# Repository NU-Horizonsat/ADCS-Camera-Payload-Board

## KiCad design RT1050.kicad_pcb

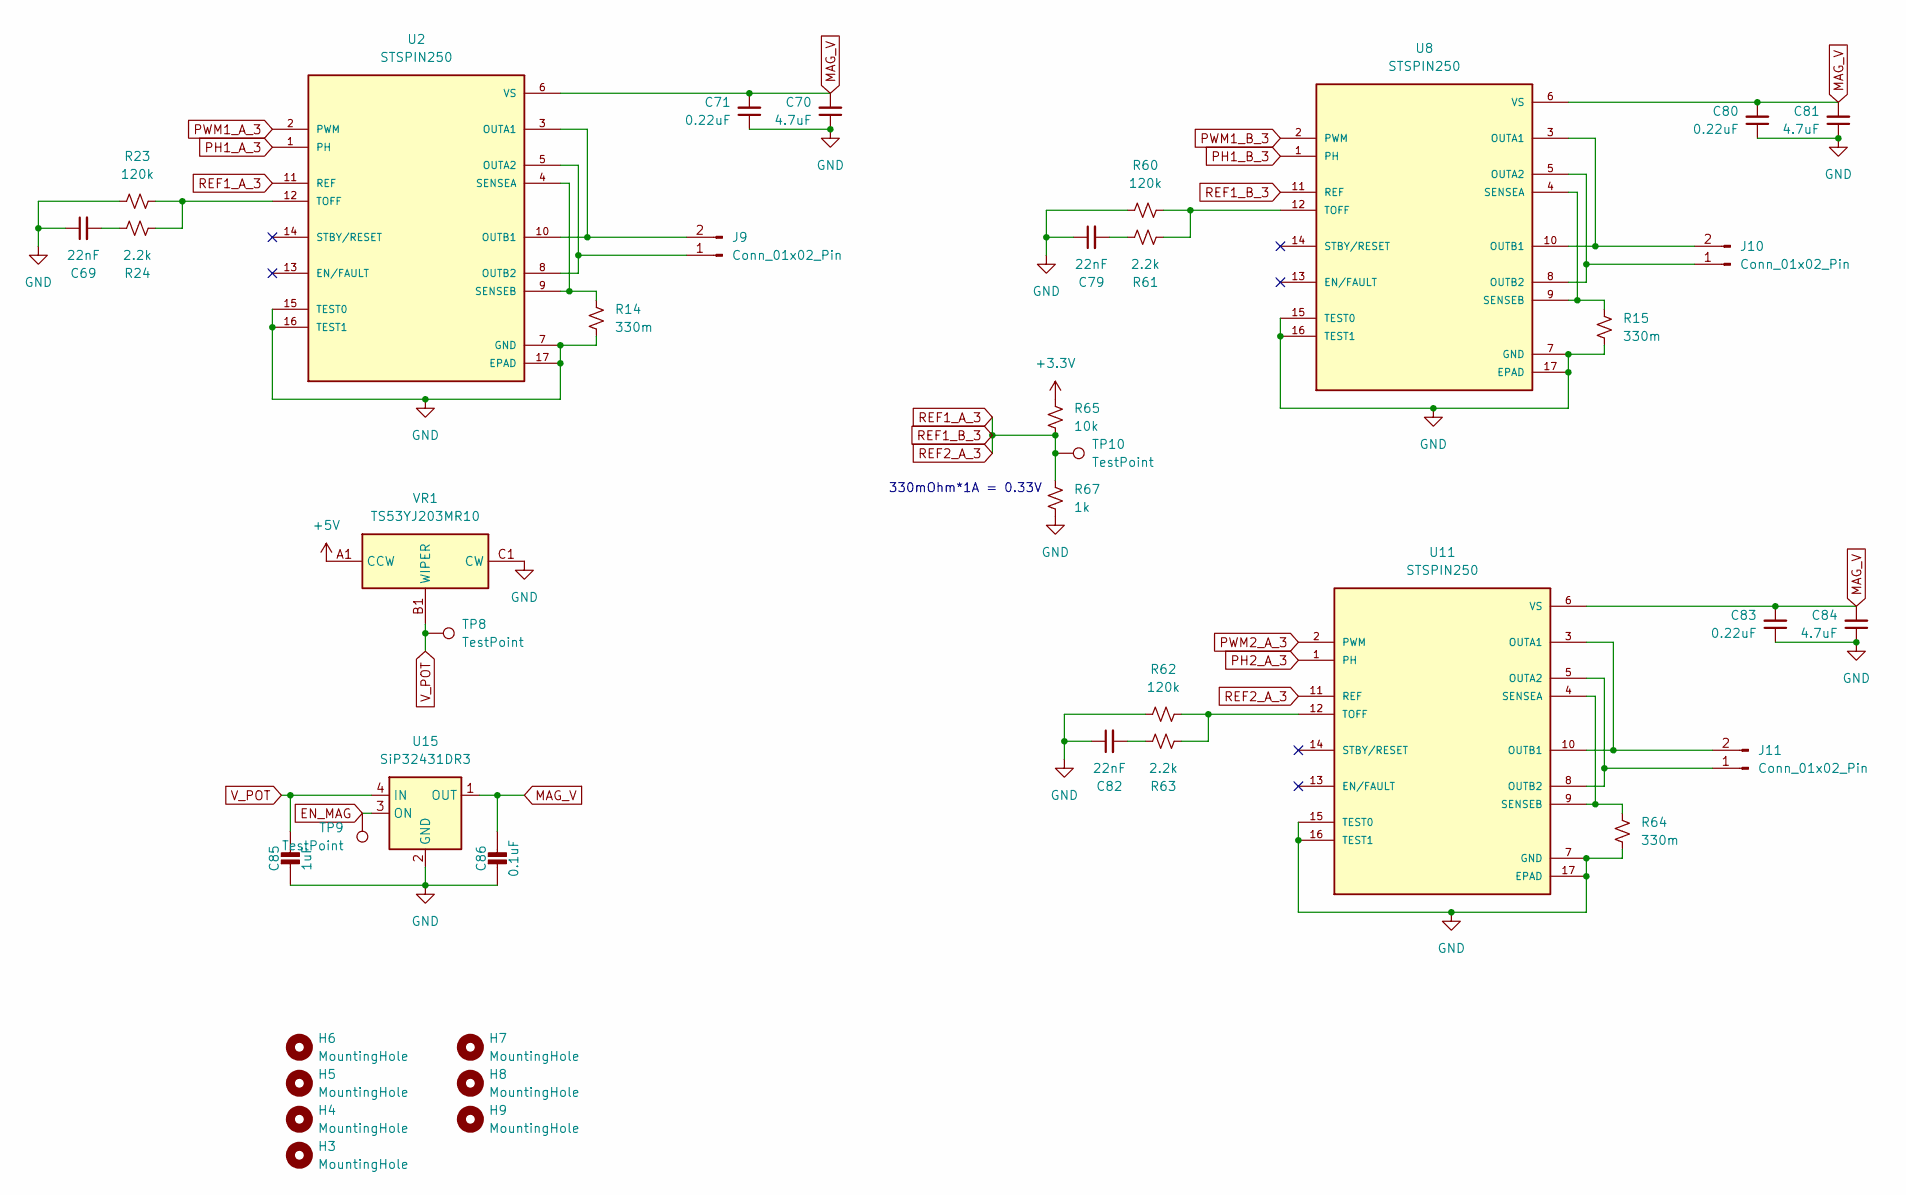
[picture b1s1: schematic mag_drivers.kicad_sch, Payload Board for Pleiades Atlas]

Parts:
C69, C79, C82: 22nF; C_0201_0603Metric
C70, C81, C84: 4.7uF; C_0201_0603Metric
C71, C80, C83: 0.22uF; C_0201_0603Metric
C85: 1uF; C_0402_1005Metric
C86: 0.1uF; C_0402_1005Metric
H3, H4, H5, H6, H7, H8, H9: MountingHole; MountingHole_2.5mm_Pad
J9, J10, J11: Conn_01x02_Pin; JST_SH_BM02B-SRSS-TB_1x02-1MP_P1.00mm_Vertical
R14, R15, R64: 330m; R_0402_1005Metric
R23, R60, R62: 120k; R_0402_1005Metric
R24, R61, R63: 2.2k; R_0402_1005Metric
R65: 10k; R_0402_1005Metric
R67: 1k; R_0402_1005Metric
TP8, TP9, TP10: TestPoint; TestPoint_Pad_D1.5mm
U2, U8, U11: STSPIN250; QFN50P300X300X100-17N; PARTREV 2
U15: SiP32431DR3; SOT-363_SC-70-6
VR1: TS53YJ203MR10; Mouser Part Number 72-TS53YJ-20K

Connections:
EN_MAG: TP9.1, U15.3 (ON); also elsewhere on the board
GND: C69.1, C70.1, C71.1, C79.1, C80.1, C81.1, C82.1, C83.1, C84.1, C85.2, C86.2, R14.2, R15.2, R23.1, R60.1, R62.1, R64.2, R67.1, U2.7 (GND), U2.15 (TEST0), U2.16 (TEST1), U2.17 (EPAD), U8.7 (GND), U8.15 (TEST0), U8.16 (TEST1), U8.17 (EPAD), U11.7 (GND), U11.15 (TEST0), U11.16 (TEST1), U11.17 (EPAD), U15.2 (GND), U15.5 (GND), VR1.C1 (CW); also elsewhere on the board
MAG_V: C70.2, C71.2, C80.2, C81.2, C83.2, C84.2, C86.1, U2.6 (VS), U8.6 (VS), U11.6 (VS), U15.1 (OUT)
unnamed: C69.2, R24.2
unnamed: C79.2, R61.2
unnamed: C82.2, R63.2
unnamed: J9.1, U2.5 (OUTA2), U2.8 (OUTB2)
unnamed: J9.2, U2.3 (OUTA1), U2.10 (OUTB1)
unnamed: J10.1, U8.5 (OUTA2), U8.8 (OUTB2)
unnamed: J10.2, U8.3 (OUTA1), U8.10 (OUTB1)
unnamed: J11.1, U11.5 (OUTA2), U11.8 (OUTB2)
unnamed: J11.2, U11.3 (OUTA1), U11.10 (OUTB1)
unnamed: R14.1, U2.4 (SENSEA), U2.9 (SENSEB)
unnamed: R23.2, R24.1, U2.12 (TOFF)
unnamed: R15.1, U8.4 (SENSEA), U8.9 (SENSEB)
unnamed: R60.2, R61.1, U8.12 (TOFF)
unnamed: R64.1, U11.4 (SENSEA), U11.9 (SENSEB)
unnamed: R62.2, R63.1, U11.12 (TOFF)
PH1_A_3: U2.1 (PH); also elsewhere on the board
PH1_B_3: U8.1 (PH); also elsewhere on the board
PH2_A_3: U11.1 (PH); also elsewhere on the board
PWM1_A_3: U2.2 (PWM); also elsewhere on the board
PWM1_B_3: U8.2 (PWM); also elsewhere on the board
PWM2_A_3: U11.2 (PWM); also elsewhere on the board
REF1_A_3: R65.1, R67.2, TP10.1, U2.11 (REF), U8.11 (REF), U11.11 (REF)
VBUS: VR1.A1 (CCW); also elsewhere on the board
V_POT: C85.1, TP8.1, U15.4 (IN), VR1.B1 (WIPER)

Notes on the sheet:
330mOhm*1A = 0.33V

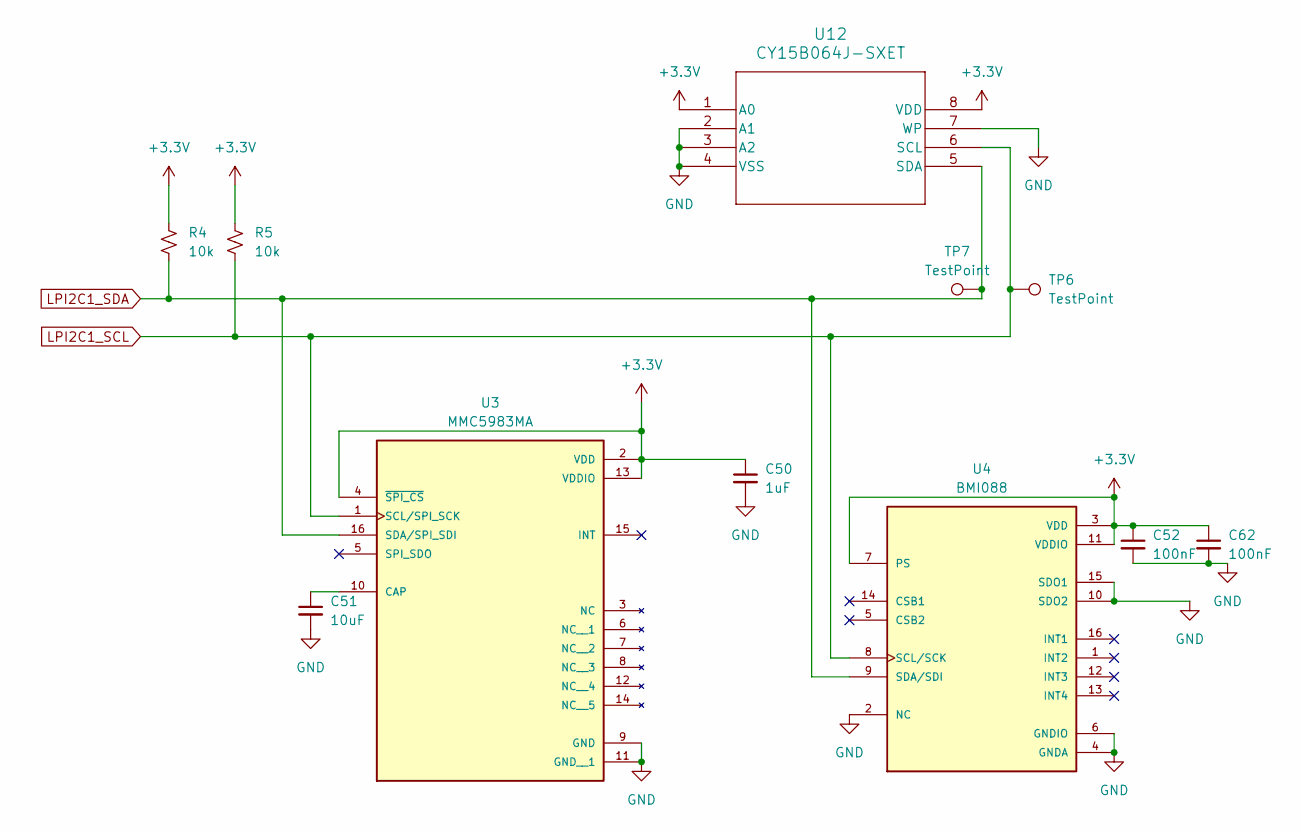
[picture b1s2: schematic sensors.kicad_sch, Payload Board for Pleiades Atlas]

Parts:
C50: 1uF; C_0201_0603Metric
C51: 10uF; C_0402_1005Metric
C52, C62: 100nF; C_0201_0603Metric
R4, R5: 10k; R_0402_1005Metric
TP6, TP7: TestPoint; TestPoint_Pad_D1.5mm
U3: MMC5983MA; MMC5983MA_MEM; PARTREV A
U4: BMI088; QFN_BMI085_BOS
U12: CY15B064J-SXET; SO8_CY15_CYP

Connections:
GND: C50.2, C51.2, C52.2, C62.2, U3.9 (GND), U3.11 (GND__1), U4.2 (NC), U4.4 (GNDA), U4.6 (GNDIO), U4.10 (SDO2), U4.15 (SDO1), U12.2 (A1), U12.3 (A2), U12.4 (VSS), U12.7 (WP); also elsewhere on the board
LPI2C1_SCL: R5.2, TP6.1, U3.1 (SCL/SPI_SCK), U4.8 (SCL/SCK), U12.6 (SCL); also elsewhere on the board
LPI2C1_SDA: R4.2, TP7.1, U3.16 (SDA/SPI_SDI), U4.9 (SDA/SDI), U12.5 (SDA); also elsewhere on the board
unnamed: C51.1, U3.10 (CAP)

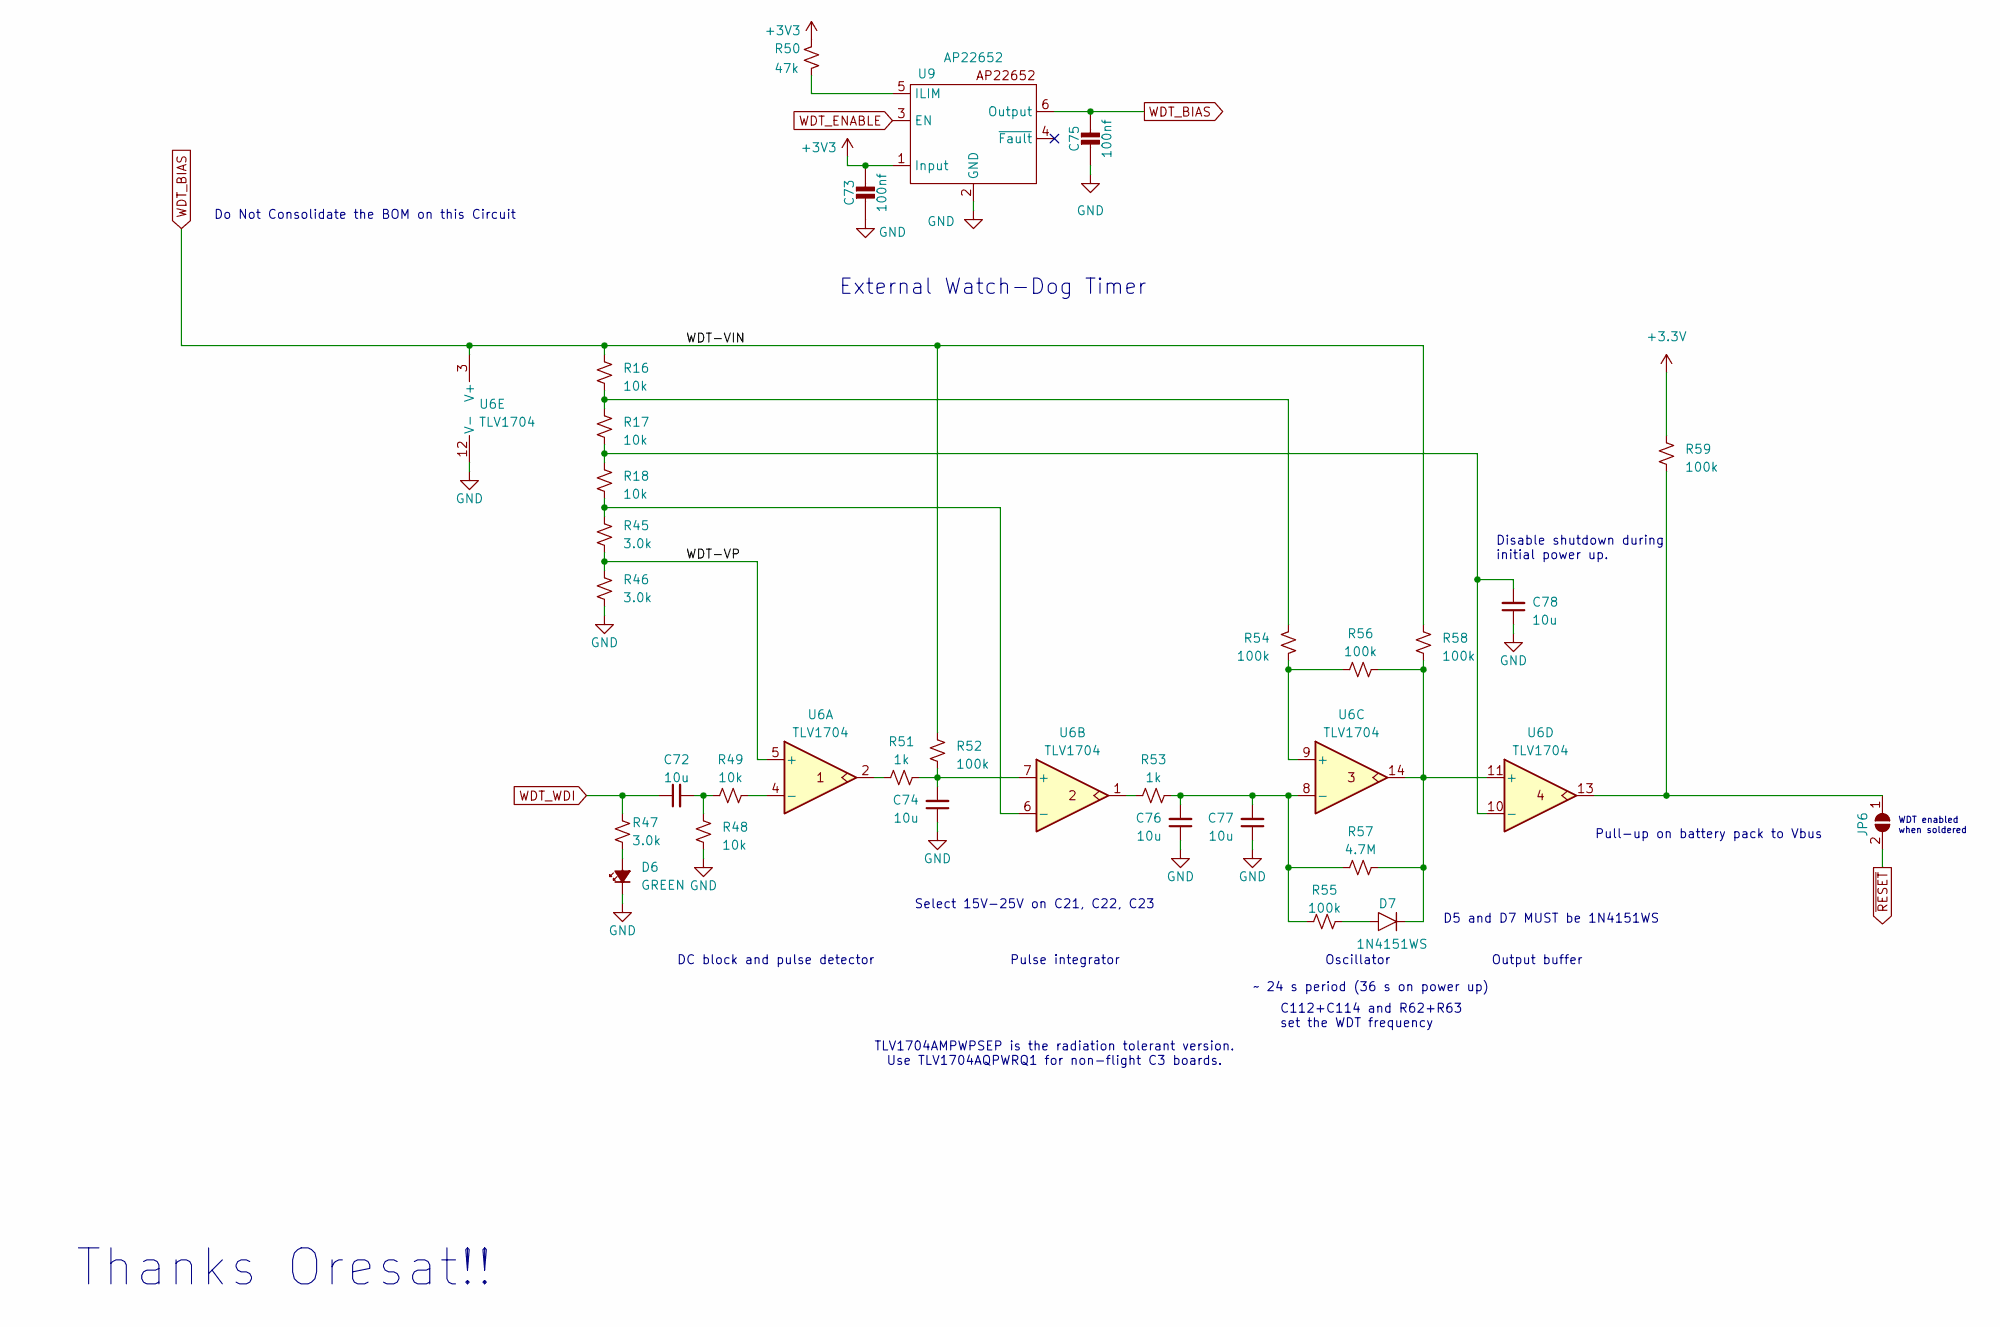
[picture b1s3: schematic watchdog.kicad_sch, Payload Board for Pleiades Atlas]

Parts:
C72, C74, C76, C77, C78: 10u; C_0603_1608Metric; MPN GRT188R61C106KE13D
C73, C75: 100nf; C_0402_1005Metric
D6: GREEN; LED_0603_1608Metric; MPN 150060GS75000
D7: 1N4151WS; D_SOD-323; MPN 1N4151WS-E3-08
JP6: SolderJumper_2_Open; SolderJumper-2_P1.3mm_Open_RoundedPad1.0x1.5mm
R16, R17, R18, R48, R49: 10k; R_0402_1005Metric; MPN RMCF0603FT10K0
R45, R46, R47: 3.0k; R_0402_1005Metric; MPN RMCF0603FT3K00
R50: 47k; R_0402_1005Metric; MPN RMCF0603FT47K0
R51, R53: 1k; R_0402_1005Metric; MPN RMCF0603FT1K00
R52, R54, R55, R56, R58, R59: 100k; R_0402_1005Metric; MPN RMCF0603FT100K
R57: 4.7M; R_0402_1005Metric; MPN RMCF0603FT4M70
U6: TLV1704; TSSOP-14_4.4x5mm_P0.65mm; MPN TLV1704AQPWRQ1
U9: AP22652; SOT95P280X145-6N

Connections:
/Watchdog/WDT-VP: R45.2, R46.1, U6.5 (+)
GND: C73.2, C74.1, C75.2, C76.1, C77.1, C78.1, D6.1 (K), R46.2, R48.2, U6.12 (V-), U9.2 (GND); also elsewhere on the board
unnamed: C72.2, R48.1, R49.1
unnamed: D6.2 (A), R47.2
unnamed: D7.2, R55.1
unnamed: JP6.1 (A), R59.1, U6.13
unnamed: R16.2, R17.1, R54.2
unnamed: R51.1, U6.2
unnamed: R53.1, U6.1
unnamed: R49.2, U6.4 (-)
unnamed: C74.2, R51.2, R52.2, U6.7 (+)
unnamed: R18.2, R45.1, U6.6 (-)
unnamed: R54.1, R56.1, U6.9 (+)
unnamed: C76.2, C77.2, R53.2, R55.2, R57.2, U6.8 (-)
unnamed: D7.1, R56.2, R57.1, R58.1, U6.11 (+), U6.14
unnamed: C78.2, R17.2, R18.1, U6.10 (-)
unnamed: R50.2, U9.5 (ILIM)
WDT_BIAS: C75.1, R16.1, R52.1, R58.2, U6.3 (V+), U9.6 (Output)
WDT_ENABLE: U9.3 (EN); also elsewhere on the board
WDT_WDI: C72.1, R47.1; also elsewhere on the board
~RESET: JP6.2 (B); also elsewhere on the board

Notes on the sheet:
Disable shutdown during initial power up.
WDT enabled when soldered
DC block and pulse detector
Thanks Oresat!!
Select 15V-25V on C21, C22, C23
Pulse integrator
~ 24 s period (36 s on power up)
C112+C114 and R62+R63 set the WDT frequency
Oscillator
TLV1704AMPWPSEP is the radiation tolerant version. Use TLV1704AQPWRQ1 for non-flight C3 boards.
Output buffer
Do Not Consolidate the BOM on this Circuit
Pull-up on battery pack to Vbus
External Watch-Dog Timer
D5 and D7 MUST be 1N4151WS

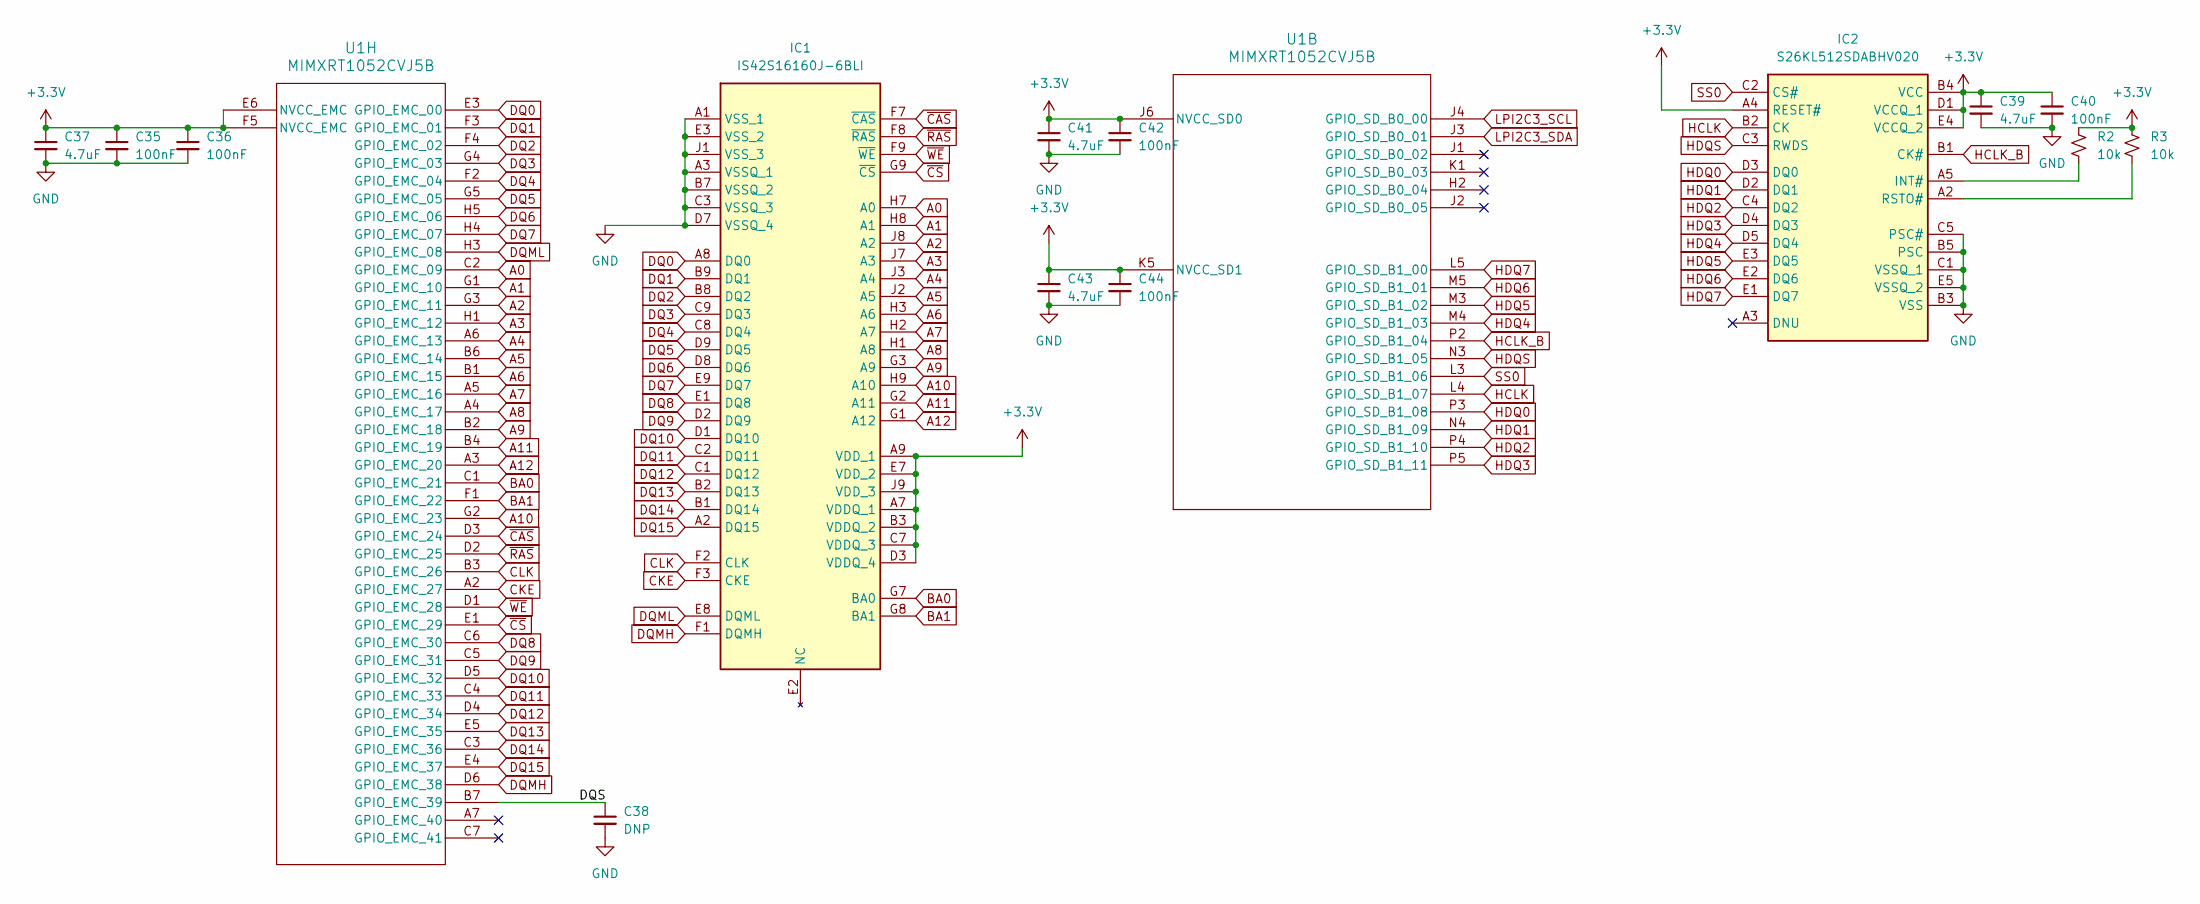
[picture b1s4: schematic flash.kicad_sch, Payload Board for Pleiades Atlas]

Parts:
C35, C36, C40, C42, C44: 100nF; C_0201_0603Metric
C37, C39, C41, C43: 4.7uF; C_0201_0603Metric
C38: DNP; C_0201_0603Metric
IC1: IS42S16160J-6BLI; BGA54C80P9X9_800X800X120; Mouser Part Number 870-42S16160J6BLI
IC2: S26KL512SDABHV020; BGA24C100P5X5_600X800X100; Mouser Part Number 727-26KS512SDPBHV020
R2, R3: 10k; R_0402_1005Metric
U1: MIMXRT1052CVJ5B; MAPBGA196_12X12

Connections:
/Flash & Memory/DQS: C38.1, U1.B7 (GPIO_EMC_39)
A0: IC1.H7 (A0), U1.C2 (GPIO_EMC_09)
A1: IC1.H8 (A1), U1.G1 (GPIO_EMC_10)
A2: IC1.J8 (A2), U1.G3 (GPIO_EMC_11)
A3: IC1.J7 (A3), U1.H1 (GPIO_EMC_12)
A4: IC1.J3 (A4), U1.A6 (GPIO_EMC_13)
A5: IC1.J2 (A5), U1.B6 (GPIO_EMC_14)
A6: IC1.H3 (A6), U1.B1 (GPIO_EMC_15)
A7: IC1.H2 (A7), U1.A5 (GPIO_EMC_16)
A8: IC1.H1 (A8), U1.A4 (GPIO_EMC_17)
A9: IC1.G3 (A9), U1.B2 (GPIO_EMC_18)
A10: IC1.H9 (A10), U1.G2 (GPIO_EMC_23)
A11: IC1.G2 (A11), U1.B4 (GPIO_EMC_19)
A12: IC1.G1 (A12), U1.A3 (GPIO_EMC_20)
BA0: IC1.G7 (BA0), U1.C1 (GPIO_EMC_21)
BA1: IC1.G8 (BA1), U1.F1 (GPIO_EMC_22)
CKE: IC1.F3 (CKE), U1.A2 (GPIO_EMC_27)
CLK: IC1.F2 (CLK), U1.B3 (GPIO_EMC_26)
DQ0: IC1.A8 (DQ0), U1.E3 (GPIO_EMC_00)
DQ1: IC1.B9 (DQ1), U1.F3 (GPIO_EMC_01)
DQ2: IC1.B8 (DQ2), U1.F4 (GPIO_EMC_02)
DQ3: IC1.C9 (DQ3), U1.G4 (GPIO_EMC_03)
DQ4: IC1.C8 (DQ4), U1.F2 (GPIO_EMC_04)
DQ5: IC1.D9 (DQ5), U1.G5 (GPIO_EMC_05)
DQ6: IC1.D8 (DQ6), U1.H5 (GPIO_EMC_06)
DQ7: IC1.E9 (DQ7), U1.H4 (GPIO_EMC_07)
DQ8: IC1.E1 (DQ8), U1.C6 (GPIO_EMC_30)
DQ9: IC1.D2 (DQ9), U1.C5 (GPIO_EMC_31)
DQ10: IC1.D1 (DQ10), U1.D5 (GPIO_EMC_32)
DQ11: IC1.C2 (DQ11), U1.C4 (GPIO_EMC_33)
DQ12: IC1.C1 (DQ12), U1.D4 (GPIO_EMC_34)
DQ13: IC1.B2 (DQ13), U1.E5 (GPIO_EMC_35)
DQ14: IC1.B1 (DQ14), U1.C3 (GPIO_EMC_36)
DQ15: IC1.A2 (DQ15), U1.E4 (GPIO_EMC_37)
DQMH: IC1.F1 (DQMH), U1.D6 (GPIO_EMC_38)
DQML: IC1.E8 (DQML), U1.H3 (GPIO_EMC_08)
GND: C35.2, C36.2, C37.2, C38.2, C39.2, C40.2, C41.2, C42.2, C43.2, C44.2, IC1.A1 (VSS_1), IC1.A3 (VSSQ_1), IC1.B7 (VSSQ_2), IC1.C3 (VSSQ_3), IC1.D7 (VSSQ_4), IC1.E3 (VSS_2), IC1.J1 (VSS_3), IC2.B3 (VSS), IC2.B5 (PSC), IC2.C1 (VSSQ_1), IC2.C5 (PSC#), IC2.E5 (VSSQ_2); also elsewhere on the board
HCLK: IC2.B2 (CK), U1.L4 (GPIO_SD_B1_07)
HCLK_B: IC2.B1 (CK#), U1.P2 (GPIO_SD_B1_04)
HDQ0: IC2.D3 (DQ0), U1.P3 (GPIO_SD_B1_08)
HDQ1: IC2.D2 (DQ1), U1.N4 (GPIO_SD_B1_09)
HDQ2: IC2.C4 (DQ2), U1.P4 (GPIO_SD_B1_10)
HDQ3: IC2.D4 (DQ3), U1.P5 (GPIO_SD_B1_11)
HDQ4: IC2.D5 (DQ4), U1.M4 (GPIO_SD_B1_03)
HDQ5: IC2.E3 (DQ5), U1.M3 (GPIO_SD_B1_02)
HDQ6: IC2.E2 (DQ6), U1.M5 (GPIO_SD_B1_01)
HDQ7: IC2.E1 (DQ7), U1.L5 (GPIO_SD_B1_00)
HDQS: IC2.C3 (RWDS), U1.N3 (GPIO_SD_B1_05)
LPI2C3_SCL: U1.J4 (GPIO_SD_B0_00); also elsewhere on the board
LPI2C3_SDA: U1.J3 (GPIO_SD_B0_01); also elsewhere on the board
unnamed: IC2.A5 (INT#), R2.2
unnamed: IC2.A2 (RSTO#), R3.2
SS0: IC2.C2 (CS#), U1.L3 (GPIO_SD_B1_06)
~CAS: IC1.F7 (~CAS), U1.D3 (GPIO_EMC_24)
~CS: IC1.G9 (~CS), U1.E1 (GPIO_EMC_29)
~RAS: IC1.F8 (~RAS), U1.D2 (GPIO_EMC_25)
~WE: IC1.F9 (~WE), U1.D1 (GPIO_EMC_28)

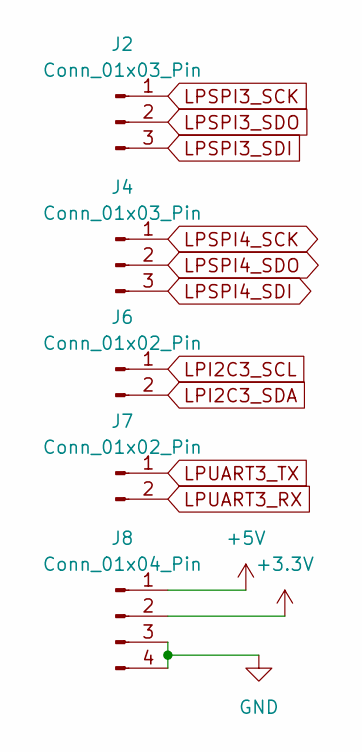
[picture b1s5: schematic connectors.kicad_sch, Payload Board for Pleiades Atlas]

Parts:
J2, J4: Conn_01x03_Pin; PinHeader_1x03_P2.54mm_Vertical
J6, J7: Conn_01x02_Pin; PinHeader_1x02_P2.54mm_Vertical
J8: Conn_01x04_Pin; PinHeader_1x04_P2.54mm_Vertical

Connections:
GND: J8.3, J8.4; also elsewhere on the board
GPIO_B0_08: J7.1; also elsewhere on the board
GPIO_B0_09: J7.2; also elsewhere on the board
LPI2C3_SCL: J6.1; also elsewhere on the board
LPI2C3_SDA: J6.2; also elsewhere on the board
LPSPI3_SCK: J2.1; also elsewhere on the board
LPSPI3_SDI: J2.3; also elsewhere on the board
LPSPI3_SDO: J2.2; also elsewhere on the board
LPSPI4_SCK: J4.1; also elsewhere on the board
LPSPI4_SDI: J4.3; also elsewhere on the board
LPSPI4_SDO: J4.2; also elsewhere on the board
VBUS: J8.1; also elsewhere on the board

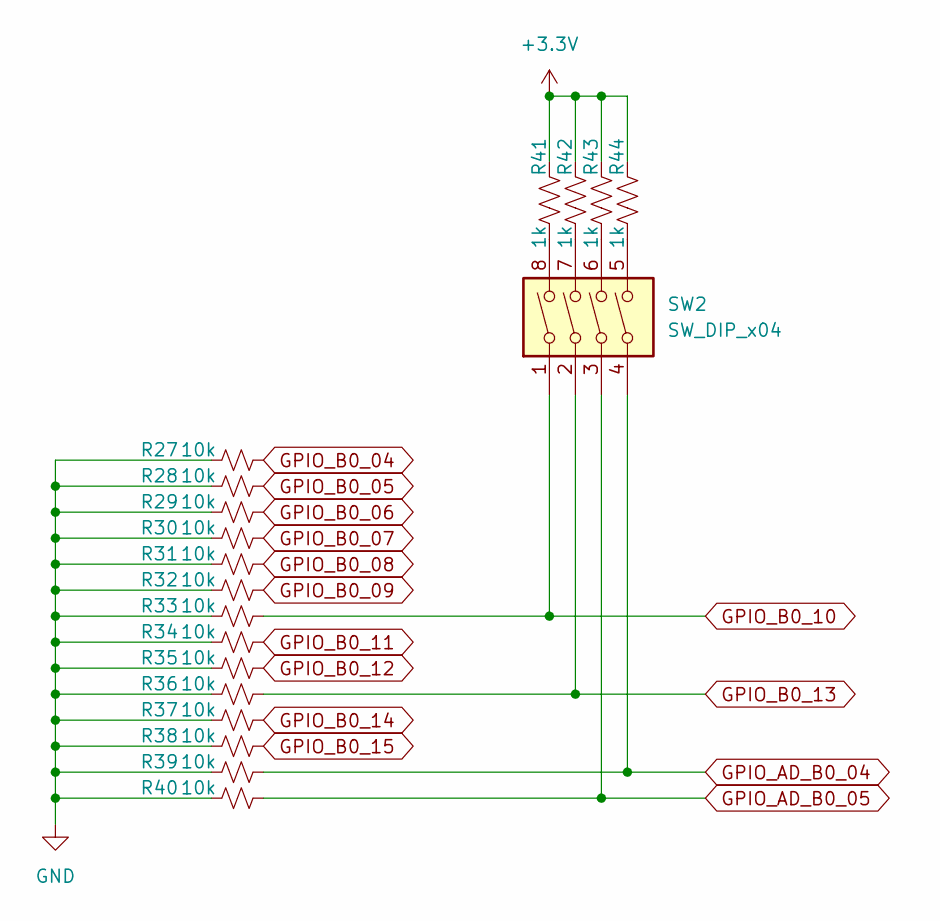
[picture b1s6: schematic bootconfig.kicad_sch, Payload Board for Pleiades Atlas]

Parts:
R27, R28, R29, R30, R31, R32, R33, R34, R35, R36, R37, R38, R39, R40: 10k; R_0402_1005Metric
R41, R42, R43, R44: 1k; R_0402_1005Metric
SW2: SW_DIP_x04; SW_DIP_SPSTx04_Slide_Copal_CHS-04A_W5.08mm_P1.27mm_JPin

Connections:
GND: R27.1, R28.1, R29.1, R30.1, R31.1, R32.1, R33.1, R34.1, R35.1, R36.1, R37.1, R38.1, R39.1, R40.1; also elsewhere on the board
GPIO_AD_B0_04: R39.2, SW2.4; also elsewhere on the board
GPIO_AD_B0_05: R40.2, SW2.3; also elsewhere on the board
GPIO_B0_04: R27.2; also elsewhere on the board
GPIO_B0_05: R28.2; also elsewhere on the board
GPIO_B0_06: R29.2; also elsewhere on the board
GPIO_B0_07: R30.2; also elsewhere on the board
GPIO_B0_08: R31.2; also elsewhere on the board
GPIO_B0_09: R32.2; also elsewhere on the board
GPIO_B0_10: R33.2, SW2.1; also elsewhere on the board
GPIO_B0_11: R34.2; also elsewhere on the board
GPIO_B0_12: R35.2; also elsewhere on the board
GPIO_B0_13: R36.2, SW2.2; also elsewhere on the board
GPIO_B0_14: R37.2; also elsewhere on the board
GPIO_B0_15: R38.2; also elsewhere on the board
unnamed: R41.2, SW2.8
unnamed: R42.2, SW2.7
unnamed: R43.2, SW2.6
unnamed: R44.2, SW2.5

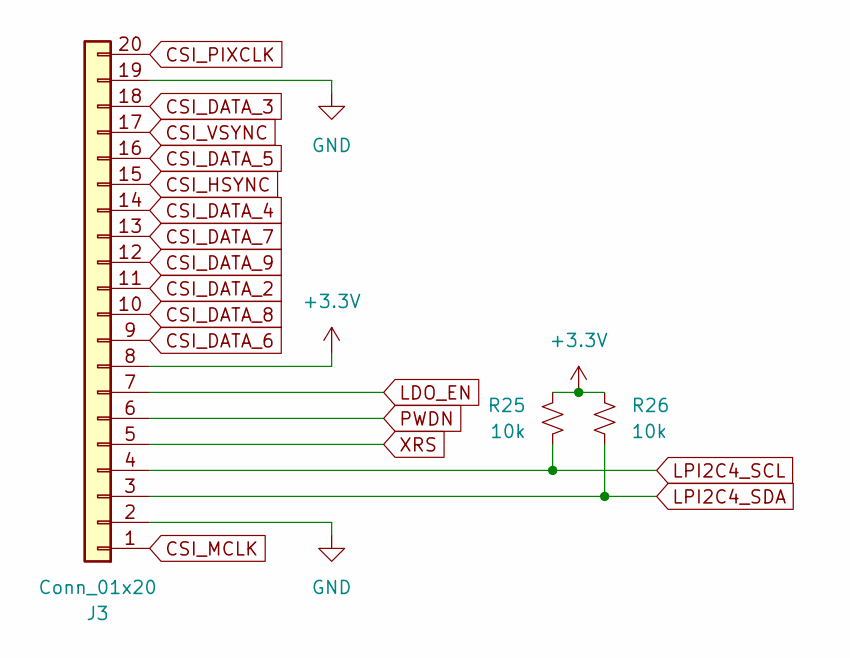
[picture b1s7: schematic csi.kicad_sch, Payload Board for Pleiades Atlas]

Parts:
J3: Conn_01x20; TE_2-1734839-0_1x20-1MP_P0.5mm_Horizontal
R25, R26: 10k; R_0402_1005Metric

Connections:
CSI_DATA_2: J3.11; also elsewhere on the board
CSI_DATA_3: J3.18; also elsewhere on the board
CSI_DATA_4: J3.14; also elsewhere on the board
CSI_DATA_5: J3.16; also elsewhere on the board
CSI_DATA_6: J3.9; also elsewhere on the board
CSI_DATA_7: J3.13; also elsewhere on the board
CSI_DATA_8: J3.10; also elsewhere on the board
CSI_DATA_9: J3.12; also elsewhere on the board
CSI_HSYNC: J3.15; also elsewhere on the board
CSI_MCLK: J3.1; also elsewhere on the board
CSI_PIXCLK: J3.20; also elsewhere on the board
CSI_VSYNC: J3.17; also elsewhere on the board
GND: J3.2, J3.19; also elsewhere on the board
LDO_EN: J3.7; also elsewhere on the board
LPI2C4_SCL: J3.4, R25.2; also elsewhere on the board
LPI2C4_SDA: J3.3, R26.2; also elsewhere on the board
PWDN: J3.6; also elsewhere on the board
XRS: J3.5; also elsewhere on the board

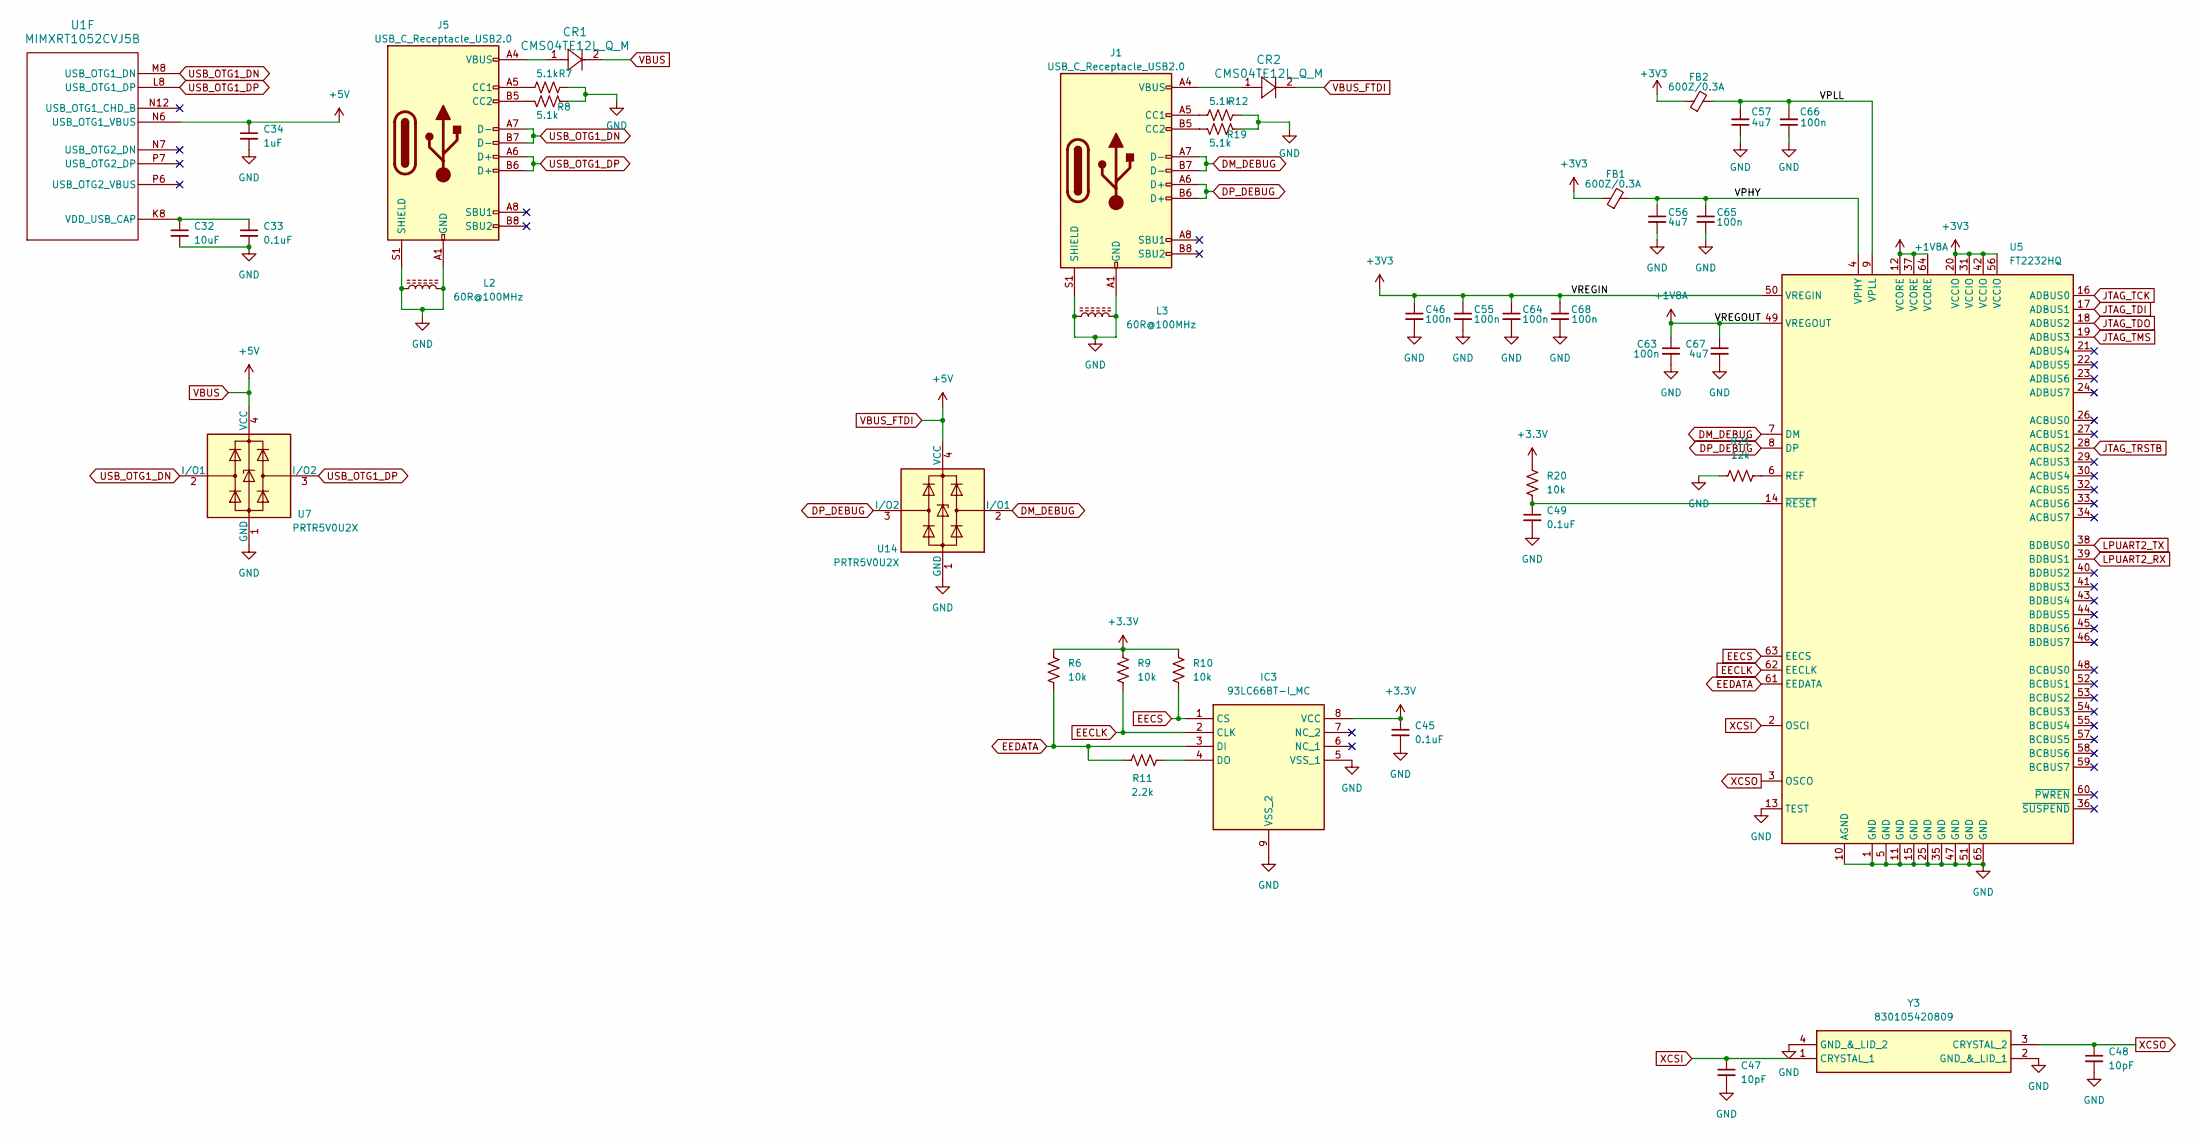
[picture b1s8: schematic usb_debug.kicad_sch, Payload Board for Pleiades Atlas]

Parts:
C32: 10uF; C_0402_1005Metric
C33, C45, C49: 0.1uF; C_0201_0603Metric
C34: 1uF; C_0201_0603Metric
C46, C55, C63, C64, C65, C66, C68: C_100n_16V_X7R_0402; C_0402_1005Metric; Voltage 16V; MPN C0402C104J4RAC7411
C47, C48: 10pF; C_0201_0603Metric
C56, C57, C67: C_4u7_0402; C_0402_1005Metric; MPN GRM155R61A475MEAAD
CR1, CR2: CMS04TE12L_Q_M; M-FLAT_TOS
FB1, FB2: FB_600Z_0.3A_Murata-BLM15AG_0402; L_0402_1005Metric; MPN BLM15AG601SN1D
IC3: 93LC66BT-I_MC; SON50P300X200X100-9N-D; Mouser Part Number 579-93LC66BT-I/MC
J1, J5: USB_C_Receptacle_USB2.0; USB_C_Receptacle_HRO_TYPE-C-31-M-12; JlcRotOffset 180
L2, L3: 60R@100MHz; L_1206_3216Metric; Manufacturer Part No MLB3216-600P4A(f); LCSC C33600
R6, R9, R10, R20: 10k; R_0402_1005Metric
R7, R8, R12, R19: 5.1k; R_0402_1005Metric
R11: 2.2k; R_0402_1005Metric
R21: 12k; R_0402_1005Metric
U1: MIMXRT1052CVJ5B; MAPBGA196_12X12
U5: FT2232HQ; QFN-64-1EP_9x9mm_P0.5mm_EP4.35x4.35mm
U7, U14: PRTR5V0U2X; SOT-143; LCSC C2827688
Y3: 830105420809; Mouser Part Number 710-830105420809

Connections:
+1V8A: C63.1, C67.1, U5.12 (VCORE), U5.37 (VCORE), U5.49 (VREGOUT), U5.64 (VCORE)
/USB & Debug/VPHY: C56.1, C65.1, FB1.2, U5.4 (VPHY)
/USB & Debug/VPLL: C57.2, C66.2, FB2.2, U5.9 (VPLL)
DM_DEBUG: J1.A7 (D-), J1.B7 (D-), U5.7 (DM), U14.2 (I/O1)
DP_DEBUG: J1.A6 (D+), J1.B6 (D+), U5.8 (DP), U14.3 (I/O2)
EECLK: IC3.2 (CLK), R9.2, U5.62 (EECLK)
EECS: IC3.1 (CS), R10.2, U5.63 (EECS)
EEDATA: IC3.3 (DI), R6.2, R11.1, U5.61 (EEDATA)
GND: C32.2, C33.2, C34.2, C45.2, C46.2, C47.2, C48.2, C49.2, C55.2, C56.2, C57.1, C63.2, C64.2, C65.2, C66.1, C67.2, C68.2, IC3.5 (VSS_1), IC3.9 (VSS_2), J1.A1 (GND), J1.A12 (GND), J1.B1 (GND), J1.B12 (GND), J1.S1 (SHIELD), J5.A1 (GND), J5.A12 (GND), J5.B1 (GND), J5.B12 (GND), J5.S1 (SHIELD), L2.1, L2.2, L3.1, L3.2, R7.1, R8.1, R12.1, R19.1, R21.1, U5.1 (GND), U5.5 (GND), U5.10 (AGND), U5.11 (GND), U5.13 (TEST), U5.15 (GND), U5.25 (GND), U5.35 (GND), U5.47 (GND), U5.51 (GND), U5.65 (GND), U7.1 (GND), U14.1 (GND), Y3.2 (GND_&_LID_1), Y3.4 (GND_&_LID_2); also elsewhere on the board
JTAG_TCK: U5.16 (ADBUS0); also elsewhere on the board
JTAG_TDI: U5.17 (ADBUS1); also elsewhere on the board
JTAG_TDO: U5.18 (ADBUS2); also elsewhere on the board
JTAG_TMS: U5.19 (ADBUS3); also elsewhere on the board
JTAG_TRSTB: U5.28 (ACBUS2); also elsewhere on the board
LPUART2_RX: U5.39 (BDBUS1); also elsewhere on the board
LPUART2_TX: U5.38 (BDBUS0); also elsewhere on the board
unnamed: CR1.1, J5.A4 (VBUS), J5.A9 (VBUS), J5.B4 (VBUS), J5.B9 (VBUS)
unnamed: CR2.1, J1.A4 (VBUS), J1.A9 (VBUS), J1.B4 (VBUS), J1.B9 (VBUS)
unnamed: IC3.4 (DO), R11.2
unnamed: J1.A5 (CC1), R12.2
unnamed: J1.B5 (CC2), R19.2
unnamed: J5.A5 (CC1), R7.2
unnamed: J5.B5 (CC2), R8.2
unnamed: C32.1, C33.1, U1.K8 (VDD_USB_CAP)
unnamed: R21.2, U5.6 (REF)
unnamed: C49.1, R20.2, U5.14 (~RESET)
USB_OTG1_DN: J5.A7 (D-), J5.B7 (D-), U1.M8 (USB_OTG1_DN), U7.2 (I/O1)
USB_OTG1_DP: J5.A6 (D+), J5.B6 (D+), U1.L8 (USB_OTG1_DP), U7.3 (I/O2)
VBUS: C34.1, CR1.2, CR2.2, U1.N6 (USB_OTG1_VBUS), U7.4 (VCC), U14.4 (VCC); also elsewhere on the board
XCSI: C47.1, U5.2 (OSCI), Y3.1 (CRYSTAL_1)
XCSO: C48.1, U5.3 (OSCO), Y3.3 (CRYSTAL_2)

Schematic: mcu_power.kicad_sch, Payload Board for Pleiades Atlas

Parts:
C1, C2, C3, C4, C5, C6, C7, C8, C9, C11, C13, C15, C17, C18, C20, C25, C26, C27, C29, C31: 0.22uF; C_0201_0603Metric
C10, C12, C16, C19, C24: 4.7uF; C_0201_0603Metric
C14: 1uF; C_0201_0603Metric
C21, C22: 8pF; C_0201_0603Metric
C23: 18pF; C_0201_0603Metric
C28, C88: 22uF; C_0603_1608Metric
C30: 33uF; C_0805_2012Metric
C87: 10uF; C_0402_1005Metric
L1: 4.7uH; L_0603_1608Metric
L5: 2.2uH; R_0402_1005Metric
R1: 30k; R_0402_1005Metric
R66: 100k; R_0402_1005Metric
TP4, TP5: TestPoint; TestPoint_Pad_D1.5mm
U1: MIMXRT1052CVJ5B; MAPBGA196_12X12
U13: TPS62162DSG; WSON-8-1EP_2x2mm_P0.5mm_EP0.9x1.6mm_ThermalVias
Y1: DSC1001BI5-024.0000; CDFN4_5X3P2_MCH; Mouser Part Number 579-001BI50240000
Y2: 830107834801; WE-XTAL_IQXC-146; Mouser Part Number 710-830107834801

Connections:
DCDC_OUT: C1.2, C2.2, C3.2, C4.2, C5.2, C6.2, C7.2, C8.2, C9.2, C10.2, C29.2, C30.2, L1.1, TP4.1, U1.F6 (VDD_SOC_IN), U1.F7 (VDD_SOC_IN), U1.F8 (VDD_SOC_IN), U1.F9 (VDD_SOC_IN), U1.G6 (VDD_SOC_IN), U1.G9 (VDD_SOC_IN), U1.H6 (VDD_SOC_IN), U1.H9 (VDD_SOC_IN), U1.J5 (DCDC_SENSE), U1.J9 (VDD_SOC_IN)
GND: C1.1, C2.1, C3.1, C4.1, C5.1, C6.1, C7.1, C8.1, C9.1, C10.1, C11.1, C12.1, C13.1, C14.1, C15.1, C16.1, C17.1, C18.1, C19.1, C20.1, C21.2, C22.2, C23.1, C24.1, C25.1, C26.1, C27.1, C28.1, C29.1, C30.1, C31.1, C87.2, C88.2, U1.A1 (VSS), U1.A14 (VSS), U1.B5 (VSS), U1.B10 (VSS), U1.E2 (VSS), U1.E13 (VSS), U1.G7 (VSS), U1.G8 (VSS), U1.H7 (VSS), U1.H8 (VSS), U1.J7 (VSS), U1.J8 (VSS), U1.K2 (VSS), U1.K6 (TEST_MODE), U1.K9 (NGND_KEL0), U1.K13 (VSS), U1.L9 (VSS), U1.N1 (DCDC_GND), U1.N2 (DCDC_GND), U1.N5 (VSS), U1.N8 (VSS), U1.P1 (VSS), U1.P14 (VSS), U13.1 (PGND), U13.4 (AGND), U13.5 (FB), U13.9 (PAD), Y1.2 (GND), Y2.2 (GND(LID)); also elsewhere on the board
unnamed: L1.2, U1.M1 (DCDC_LP), U1.M2 (DCDC_LP)
unnamed: C31.2, R1.1, U1.K3 (DCDC_PSWITCH)
unnamed: C21.1, U1.N9 (RTC_XTALI), Y2.1 (CRYSTAL_1)
unnamed: C22.1, U1.P9 (RTC_XTALO), Y2.3 (CRYSTAL_2)
unnamed: C23.2, U1.P11 (XTALI)
unnamed: U1.N11 (XTALO), Y1.3 (OUT)
unnamed: C19.2, C20.2, U1.P10 (NVCC_PLL)
unnamed: C11.2, C12.2, U1.P8 (VDD_HIGH_CAP)
unnamed: C15.2, U1.M10 (VDD_SNVS_CAP)
unnamed: R66.2, U13.8 (PG)
unnamed: L5.1, U13.7 (SW)
PMIC_ON_REQ: TP5.1, U1.K7 (PMIC_ON_REQ)
VBUS: C87.1, U13.2 (VIN), U13.3 (EN); also elsewhere on the board
WAKEUP: U1.L6 (WAKEUP)
~RESET: U1.M7 (POR_B); also elsewhere on the board

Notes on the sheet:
Power and DC/DC Converter
Ground

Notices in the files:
parts and their libraries:
License: Apache-2.0
